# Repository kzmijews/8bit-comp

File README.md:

# NAT-1: 8bit computer

## Overview
NAT-1 (aka NATALIE-1) is 8bit computer created based on well-known design of MARIE.
Simple computer described in "The Essentials of Computer Organization and Architecture"
book writen by Linda Null and Julia Lobur. Project was created for educational purposes.

## Status
Project is not fully functional yet. Stay tuned.

# Documentation
List of available documents:
- [Hardware Architecture Spec](doc/hw-arch-spec.md)

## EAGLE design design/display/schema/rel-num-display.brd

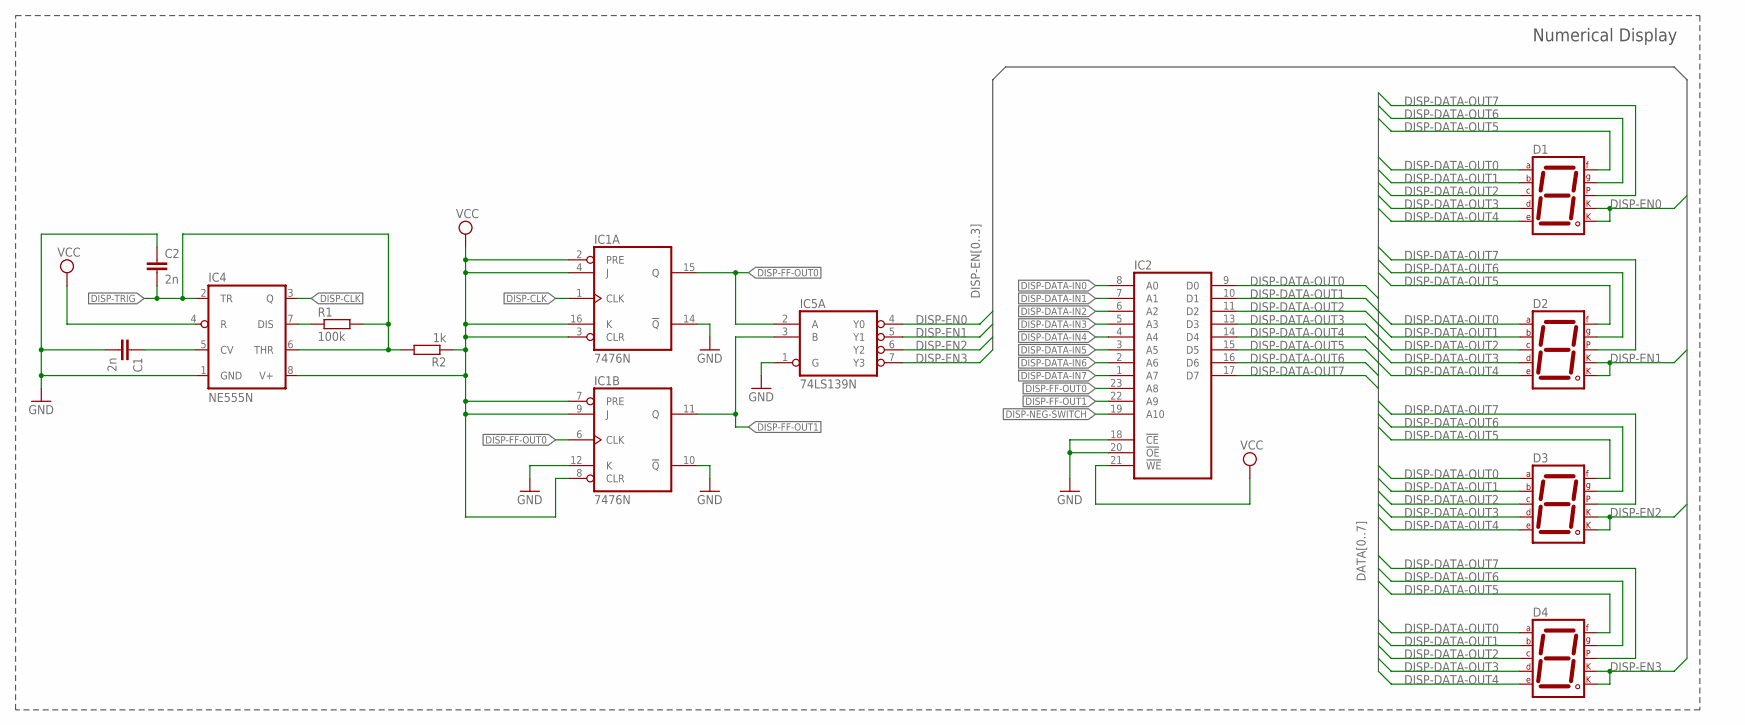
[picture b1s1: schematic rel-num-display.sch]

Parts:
C1, C2: 2n; C025-025X050
D1, D2, D3, D4: 7SEG-CK; 7SEG-13
IC1: 7476N; DIL16
IC2: 2816; DIL24
IC4: NE555N; DIL08
IC5: 74LS139N; DIL16
R1: 100k; 0204/5
R2: 1k; 0204/5

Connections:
DISP-CLK: IC1.1 (CLK), IC4.3 (Q)
DISP-DATA-IN0: IC2.8 (A0)
DISP-DATA-IN1: IC2.7 (A1)
DISP-DATA-IN2: IC2.6 (A2)
DISP-DATA-IN3: IC2.5 (A3)
DISP-DATA-IN4: IC2.4 (A4)
DISP-DATA-IN5: IC2.3 (A5)
DISP-DATA-IN6: IC2.2 (A6)
DISP-DATA-IN7: IC2.1 (A7)
DISP-DATA-OUT0: D1.7 (A), D2.7 (A), D3.7 (A), D4.7 (A), IC2.9 (D0)
DISP-DATA-OUT1: D1.6 (B), D2.6 (B), D3.6 (B), D4.6 (B), IC2.10 (D1)
DISP-DATA-OUT2: D1.4 (C), D2.4 (C), D3.4 (C), D4.4 (C), IC2.11 (D2)
DISP-DATA-OUT3: D1.2 (D), D2.2 (D), D3.2 (D), D4.2 (D), IC2.13 (D3)
DISP-DATA-OUT4: D1.1 (E), D2.1 (E), D3.1 (E), D4.1 (E), IC2.14 (D4)
DISP-DATA-OUT5: D1.9 (F), D2.9 (F), D3.9 (F), D4.9 (F), IC2.15 (D5)
DISP-DATA-OUT6: D1.10 (G), D2.10 (G), D3.10 (G), D4.10 (G), IC2.16 (D6)
DISP-DATA-OUT7: D1.5 (DP), D2.5 (DP), D3.5 (DP), D4.5 (DP), IC2.17 (D7)
DISP-EN0: D1.3 (CK1), D1.8 (CK2), IC5.4 (Y0)
DISP-EN1: D2.3 (CK1), D2.8 (CK2), IC5.5 (Y1)
DISP-EN2: D3.3 (CK1), D3.8 (CK2), IC5.6 (Y2)
DISP-EN3: D4.3 (CK1), D4.8 (CK2), IC5.7 (Y3)
DISP-FF-OUT0: IC1.6 (CLK), IC1.15 (Q), IC2.23 (A8), IC5.2 (A)
DISP-FF-OUT1: IC1.11 (Q), IC2.22 (A9), IC5.3 (B)
DISP-NEG-SWITCH: IC2.19 (A10)
DISP-TRIG: C2.2, IC4.2 (TR), IC4.6 (THR), R1.2, R2.2
GND: C1.2, C2.1, IC1.10 (!Q), IC1.12 (K), IC1.13 (GND), IC1.14 (!Q), IC2.12 (GND), IC2.18 (!CE), IC2.20 (!OE), IC4.1 (GND), IC5.1 (G), IC5.8 (GND)
unnamed: IC4.7 (DIS), R1.1
unnamed: C1.1, IC4.5 (CV)
VCC: IC1.2 (PRE), IC1.3 (CLR), IC1.4 (J), IC1.5 (VCC), IC1.7 (PRE), IC1.8 (CLR), IC1.9 (J), IC1.16 (K), IC2.21 (!WE), IC2.24 (VCC), IC4.4 (R), IC4.8 (V+), IC5.16 (VCC), R2.1

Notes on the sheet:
Numerical Display

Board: 2 copper layers, 12 parts (0 on the bottom side), 20 nets, no tracks yet.

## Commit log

2023-07-24 Added main clock schema designed with well-known timer 555
2023-07-24 Added initial version of README.md file
2023-07-29 Added initial description of main clock
2023-07-29 Added minor changes to the readme file
2023-07-29 Added minor changes - part 2
2023-07-29 Added minor changes - part 3
2023-07-29 Added minor changes - part 4
2023-07-29 Added minor changes - part 5
2023-07-29 Added main clock initial description
2023-07-29 Added main clock signal dump from oscilloscope
2023-07-29 Put clock schema into block to center img
2023-07-29 Moved clock schema to div block
2023-08-06 Added detailed description of debouncing circuit for stepping mode
2023-08-06 Fixed equation for pulse signal time of monostable timer555 used as debouncing circuit for stepping mode
2023-08-06 Stepping mode description
2023-08-06 Fixed typo - wrong symbols in hw_arch_spec description
2023-08-06 Fixed typo for symbols used in description of stepping mode
2023-10-19 Splitted clock design and other related stuff from main directory
2023-10-19 Resized schemas
2023-10-19 Resized schemas (part 2)
2023-10-19 Resized schemas (fix)
2023-10-19 Fixed path to the ltspice simulation
2023-10-20 Added initial version of clock circuit, switchable between astable and monostable mode without dbg button debouncing
2023-10-23 Added support for clock HALT signal
2023-10-23 Added description do HW arch spec of the clocking module
2023-10-23 Added description do HW arch spec of the clocking module (part 2)
2023-10-23 Added screens for debouncing of SPDT switch (S2) and SPST debug button (S1)
2023-10-23 Added missing description for SPDT and SPST debouncing
2023-11-26 Added initial version of ALU (Arithmetic Logic Unit) circuit
2023-11-26 Added missing files for ALU circuit schema
2023-12-05 Added fixes for ALU schema
2024-01-09 Changed 74LS06N which is inverter with open collector outputs into 74LS04N with standard outputs
2024-02-03 Added initial version of SRAM circuit
2024-02-03 Added main clock circuit PDF file
2024-02-04 Group ALU mux ifaces into the bus
2024-02-17 Renamed files to distinguish between release and debug version of schemas
2024-02-17 Fixed documentation links after files rename
2024-02-23 Added debug schema for SRAM circuit
2024-02-25 Added switch between programing and run modes for SRAM
2024-02-28 Fixed address switch between prog and run modes for SRAM
2024-04-09 Improve description of clock module
2024-04-09 Fixed and improved schema for SRAM module
2024-04-11 Added initial description of ALU unit
2024-04-13 Improved description of ALU unit
2024-04-13 Added initial description of main memory module (RAM)
2024-04-13 Added missing functional block diagram for RAM modules
2024-04-13 Added missing part of initial RAM module description
2024-04-28 Added initial schema for program counter
2024-05-04 Updated SRAM modules, unsed pins connected to the ground
2024-05-05 Added initial version of EEPROM programmer
2024-05-05 Moved EEPROM prog schema to proper subdirectories
2024-05-19 Removed reset pull up for eeprom prog
2024-05-30 Moved EEPROM programer to separate project
2024-06-03 Added initial eeprom program for 7segment display decoder
2024-06-03 Changed directory hierarchy
2024-06-04 Changed names for some design component directories
2024-06-04 Changed names for display images to align with the rest of files
2024-06-10 Added final fixes and program changes for numerical display
2024-06-10 Added missing numerical display schema image
2024-06-22 Added initial schema for general purpose registers
2024-06-22 Moved schema imgs to the imgs directory
2024-07-01 Aligned titles size for all schemas
2024-07-01 Added General Purpose Registers to the 8bit computer schema
2024-07-02 Connected IPs to the mainband on general schema
2024-07-07 Changed PC - SRAM connections, to enable ADDR load on DATA BUS
2024-07-08 Fixed typos for SRAM section of HAS document
2024-07-08 Fixed chip names on main schema
2024-07-08 Added initial description of General Purpose Registers to the HAS doc
2024-07-08 Fixed directory to the General Purpose Registers schema in HAS doc
2024-07-09 Resized all images/schemas for HAS doc
2024-07-12 Added overall schema of registers connection
2024-07-20 Added initial description for PC (program counter) design
2024-08-25 Added initial version of control unit schema
2024-09-29 Added separate reg for chip select of SRAM
2024-09-29 Added version number to each schema
2024-10-03 Fixed PCH in/out added CS (chip select) reg
2024-10-08 Fixed substraction arithmetic
2024-11-08 Added additional buffer to pull-up signals on diect connection to ALU
2024-11-12 Fixed ustep connections for CU, added cmd codes and CPU flags
2024-11-16 Fixed CE OE signals for CU
2024-11-16 Added initial version of FLAG register
2024-11-16 Added LEDs and buffer for flag register
2024-11-22 Added additional circuit for reset entire system
2024-11-22 Added control unit, reset circuit and flag reg to the main schema of the system
